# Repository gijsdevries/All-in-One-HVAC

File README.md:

# All-in-One-HVAC

## pythonFiles
In deze folder staan alle python bestand die wij gebruiken.  
  
[pythonFiles/MQTT_starter.py](https://github.com/gijsdevries/All-in-One-HVAC/blob/main/pythonFiles/MQTT_starter.py) als je dit script runt kan je ervoor zorgen dat de pi gaat luisteren naar MQTT data die ontvangen wordt van Home Assistent  
[pythonFiles/mqtt_reciever.py](https://github.com/gijsdevries/All-in-One-HVAC/blob/main/pythonFiles/mqtt_receiver.py) dit is het script wat de MQTT data parsed en vervolgens doorstuurt naar de HOOM unit. In dit bestand moet je zelf bepaalde waardes aan variabele toekennen. Zie hiervoor het bestand zelf. 

Zorg ervoor dat je zelf een secrets.py maakt waar je wachtwoorden etc in zet. Dit bestand staat al in de .gitignore

Daarbij staat er in deze folder ook een install guide om de juiste python omgeving op te zetten.

## testo_power
In deze folder staat het kicad bestand voor de PCB die wij hebben gemaakt. De schematic is in KiCad v10.0 gemaakt. De schematic is op dit [forum](https://electronics.stackexchange.com/questions/418090/advice-for-this-p-channel-mosfet-power-source-selector) gebasseerd.

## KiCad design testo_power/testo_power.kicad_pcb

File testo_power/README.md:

## Orders
 - v1.0, 14-5-26, ce8702

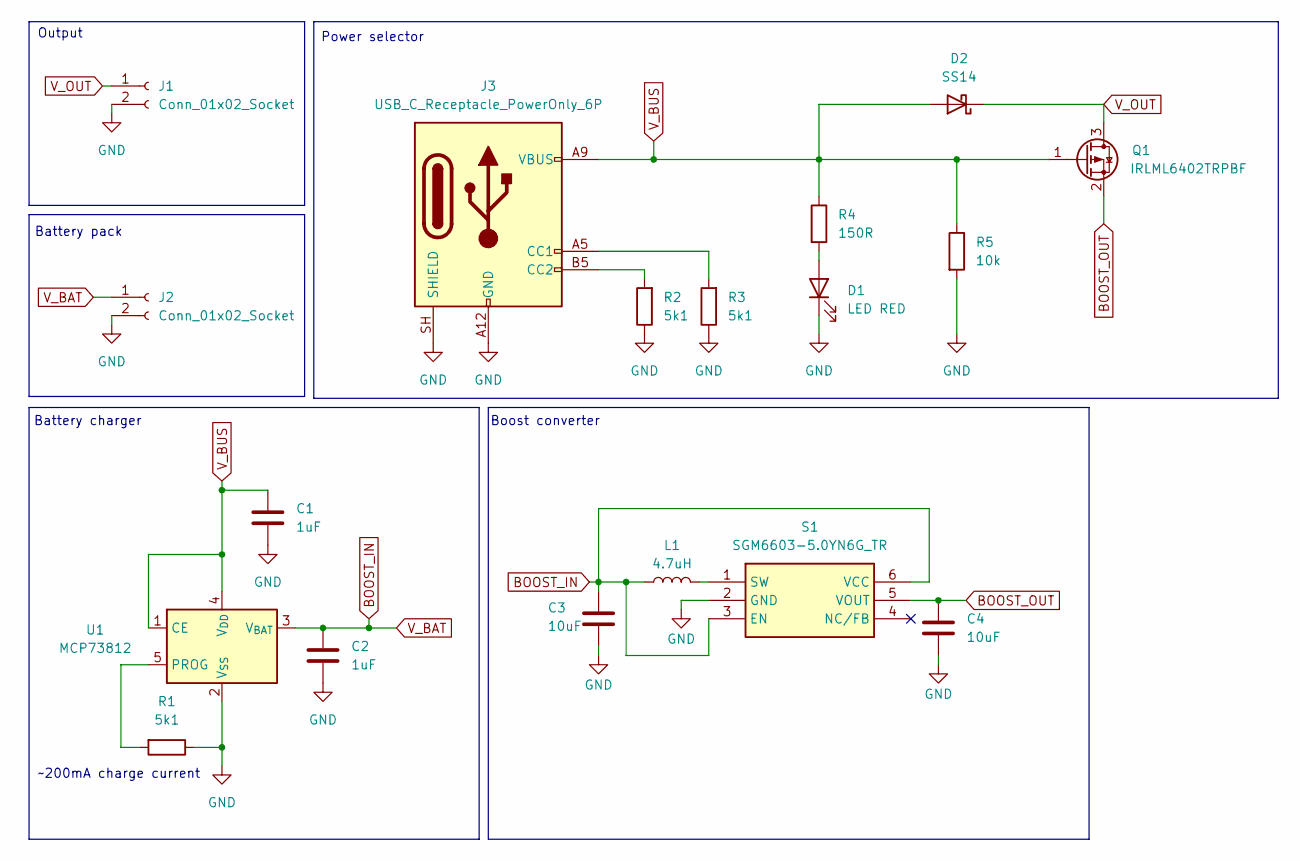
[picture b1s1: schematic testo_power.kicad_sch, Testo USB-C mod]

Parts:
C1, C2: 1uF; C_0603_1608Metric; JLC Part# C1592
C3, C4: 10uF; C_0603_1608Metric; JLC Part# C1691
D1: LED RED; LED_0603_1608Metric; JLC Part# C2286
D2: SS14; D_SMA; JLC Part# C2480
J1: Conn_01x02_Socket; PinHeader_1x02_P2.54mm_Vertical
J2: Conn_01x02_Socket; 0532610271; JLC Part# C225111
J3: USB_C_Receptacle_PowerOnly_6P; USB_C_Receptacle_HCTL_HC-TYPE-C-16P-01A; JLC Part# C165948
L1: 4.7uH; L_0805_2012Metric; JLC Part# C63166
Q1: IRLML6402TRPBF; SOT-23; JLC Part# C2593
R1, R2, R3: 5k1; R_0603_1608Metric; JLC Part# C23186
R4: 150R; R_0603_1608Metric; JLC Part# C22808
R5: 10k; R_0603_1608Metric; JLC Part# C15401
S1: SGM6603-5.0YN6G_TR; SOT95P280X125-6N; Manufacturer_Part_Number SGM6603-5.0YN6G/TR; JLC Part# C79689
U1: MCP73812; SOT-23-5; JLC Part# C144308

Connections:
BOOST_IN: C2.1, C3.1, J2.1, L1.1, S1.3 (EN), S1.6 (VCC), U1.3 (V_{BAT})
BOOST_OUT: C4.1, Q1.2 (S), S1.5 (VOUT)
GND: C1.2, C2.2, C3.2, C4.2, D1.1 (K), J1.2, J2.2, J3.A12 (GND), J3.SH (SHIELD), R1.1, R2.1, R3.1, R5.2, S1.2 (GND), U1.2 (V_{SS})
unnamed: D1.2 (A), R4.2
unnamed: J3.A5 (CC1), R3.2
unnamed: J3.B5 (CC2), R2.2
unnamed: L1.2, S1.1 (SW)
unnamed: R1.2, U1.5 (PROG)
V_BUS: C1.1, D2.2 (A), J3.A9 (VBUS), Q1.1 (G), R4.1, R5.1, U1.1 (CE), U1.4 (V_{DD})
V_OUT: D2.1 (K), J1.1, Q1.3 (D)

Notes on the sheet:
Boost converter
Output
Battery pack
~200mA charge current
Power selector
Battery charger

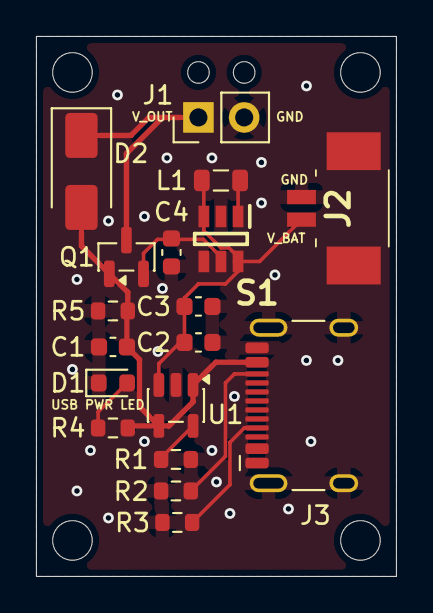
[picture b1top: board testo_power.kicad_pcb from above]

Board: 2 copper layers, 20.0 x 30.0 mm, 18 parts (0 on the bottom side), 10 nets.

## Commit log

2026-02-10 added hello world, project builds
2026-02-10 stop tracking build folder
2026-02-10 update readme
    Added project description for ESP32C6.
2026-02-10 Add gitignore as retrieved from: https://github.com/github/gitignore/blob/main/C%2B%2B.gitignore
2026-02-10 added more build files to gitignore
2026-02-10 removed build files to avoid merge conflict
2026-02-10 added another build file to ignore
2026-03-04 espidf project in separate folder
2026-03-04 added python folder and basic script
2026-03-04 basic python script
2026-03-04 usb port now USB0 instead of ACM0
2026-03-04 idk why but script runs now
2026-03-04 cleanup automatic script
2026-03-04 added ai forwarder code
2026-03-12 added txt parsing for automatic test. not tested yet
2026-03-12 cleanup
2026-03-12 added basic tests
2026-03-12 added argument parser not tested yet
2026-03-23 changed txt file and basic mqtt script works
2026-03-23 deleted forwarder file. not used
2026-03-23 recieving consistent oda eta data. not parsing it yet
2026-03-23 communicating with oda and eta
2026-03-23 added tec support
2026-03-23 parsing values correctly so script builds
2026-03-23 added possible todo
2026-03-24 parsing bool and str correct
2026-03-24 added better print statements
2026-03-24 cleanup upped code. not tested yet
2026-03-24 assinging serial_buffer with working past code
2026-03-25 script now recognizes it runs on pi
2026-03-25 push from pi??
2026-03-25 Added color to print statements
2026-03-25 Add script to enable and disable the pi forwarder script from home assistant
2026-03-25 Add usernames and password to secrets.py file
2026-03-25 removed unnsecesraresfh comment
2026-03-31 float instead of int
2026-03-31 deleted espidf project
2026-03-31 added pio project and updated gitignore
2026-04-07 only one env
2026-04-07 cleanup example. blinky
2026-04-07 removed .gitignore in pio folder
2026-04-07 deleted travisyml
2026-04-07 can connect to wifi
2026-04-07 Implement first version of TH832X reading
2026-04-08 code building now with mqtt source files
2026-04-08 connecting to wifi
2026-04-08 connecting to topic
2026-04-08 sending string to client working
2026-04-09 updated gitignore for secret file
2026-04-09 small cleanup
2026-04-09 new tasks
2026-04-09 added some comments
2026-04-09 added todo
2026-04-09 First version of SHT40 measurements with adding to queue
2026-04-13 baudrate tec now 9600
2026-04-13 copying sensor code
2026-04-13 code builds. still ugly
2026-04-13 recieving temp data in home assistent
2026-04-13 sending sensor over different topics
2026-04-13 added wifi creds to secret
2026-04-13 added valve control and turn everything off when pi enables goes down
2026-04-13 outdoor valve instead of valve
2026-04-13 new sensor file
2026-04-13 cleanupped
2026-04-13 added single comment
2026-04-13 digitalwrite now gpiosetlevel
2026-04-14 valve now 0 100 instead of true false
2026-04-15 added new variable
2026-04-15 Add valve homing
2026-04-15 added hp lp control. tested on laptop
2026-04-20 Change delay time for power circuit switching
2026-04-22 added empty kicad project
2026-04-22 Test commit for KiCad schemes
2026-04-22 modified gitignore
2026-04-22 added random component
2026-04-22 Remove useless component
2026-04-22 First schematic drawing
2026-05-06 First version of PCB design
2026-05-06 Added mounting holes, added descriptions on silkscreen, added USB power indication LED.
2026-05-07 made traces 1mm thick
2026-05-07 routed new wire
2026-05-11 pcb and schematic done
2026-05-11 added some silkscreen
2026-05-12 replaced connectors
2026-05-12 formatted schematic and added battery charger
2026-05-12 added comment for charge current
2026-05-12 Added boost converter schematic
2026-05-12 Added footprints
2026-05-12 PCB layout with charging and boost circuit
2026-05-12 Improved PCB layout for V1
2026-05-12 changed position of c2 c3
2026-05-12 Replace molex connector
2026-05-12 Add production files for ordering
2026-05-13 added water pump gi
2026-05-18 changed dir of project
2026-05-18 made readme file
2026-05-18 added readme with some basic instruction
2026-05-18 Fix formatting and improve README content
2026-05-18 removed unused files
2026-05-18 cleanup up code and added todos
2026-05-18 added one more comment
2026-05-18 Update README with python files and secrets instructions
    Added information about python files and secrets.py.
2026-05-18 Add README with Python setup instructions for Pi
    Added instructions for setting up Python environment on Raspberry Pi, including virtual environment creation and dependency installation.
2026-05-18 Update README with dependency installation and corrections
    Corrected text formatting and added installation instructions for additional dependencies.
2026-05-27 Revise Raspberry Pi installation instructions
    Updated installation instructions for Raspberry Pi.
2026-06-08 added requirements.txt to use less commands
2026-06-08 added versions of every pip package
2026-06-08 Update OS name in README for Raspberry Pi setup
2026-06-08 removed pio folder and updated readme
2026-06-08 changed letterttype
2026-06-08 added one fucking space
2026-06-08 mierenneuk shit
2026-06-08 Add comments for clarity
2026-06-08 made improvements to readme
2026-06-08 different fond in readme
2026-06-08 added some comments in readme
